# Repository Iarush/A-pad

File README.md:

# A-pad
A  custom Macropad with a special A-shaped keypad

## Specs
8 Mx Cherry Keys
EC11 Rotary Encoder
0.91" OLED Display
Seeed XIAO RP2040 Microcontroller
Custom-made PCB
Custom-made case and plates

## CAD Model

The Case is constructed using the sandwhich plating method. 3 plates were made. A bottom plate where screws are added, a middle frame amidst which the PCB rests, and finally a top switchplate for an aestheic look tht hides the screws.

### Unique Features

- Switchplate is deeply bezeled aroung the OLED to allow easier viewability
- An "island" is created at the center of the A which is compeletely seperate from other parts of the switchplate but is secured with an M3 screw.
- Rotary Encoder top is also a CAD Model
CAD was made in Onshape

## PCB Schematic

The schematic was created in KICAD with the guidance of this Joe Scotto video on matrix wiring: [Video](https://www.youtube.com/watch?v=8WXpGTIbxlQ&t=787s)

## PCB

## Firmware Overview

This hackpad uses [KMK](https://github.com/KMKfw/kmk_firmware) firmware (CircuitPython). The firmware is [Production/main.py](Production/main.py).

- The 8 keys are wired as a 3x3 diode matrix (the encoder push button is the 9th spot)
- Keys: copy / play-pause / paste on top, undo / save / redo on the crossbar, previous / next track on the legs
- The rotary encoder changes volume, press to mute
- The 8 SK6812 MINI-E LEDs run a breathing rainbow
- The OLED shows the A-Pad name and the encoder controls

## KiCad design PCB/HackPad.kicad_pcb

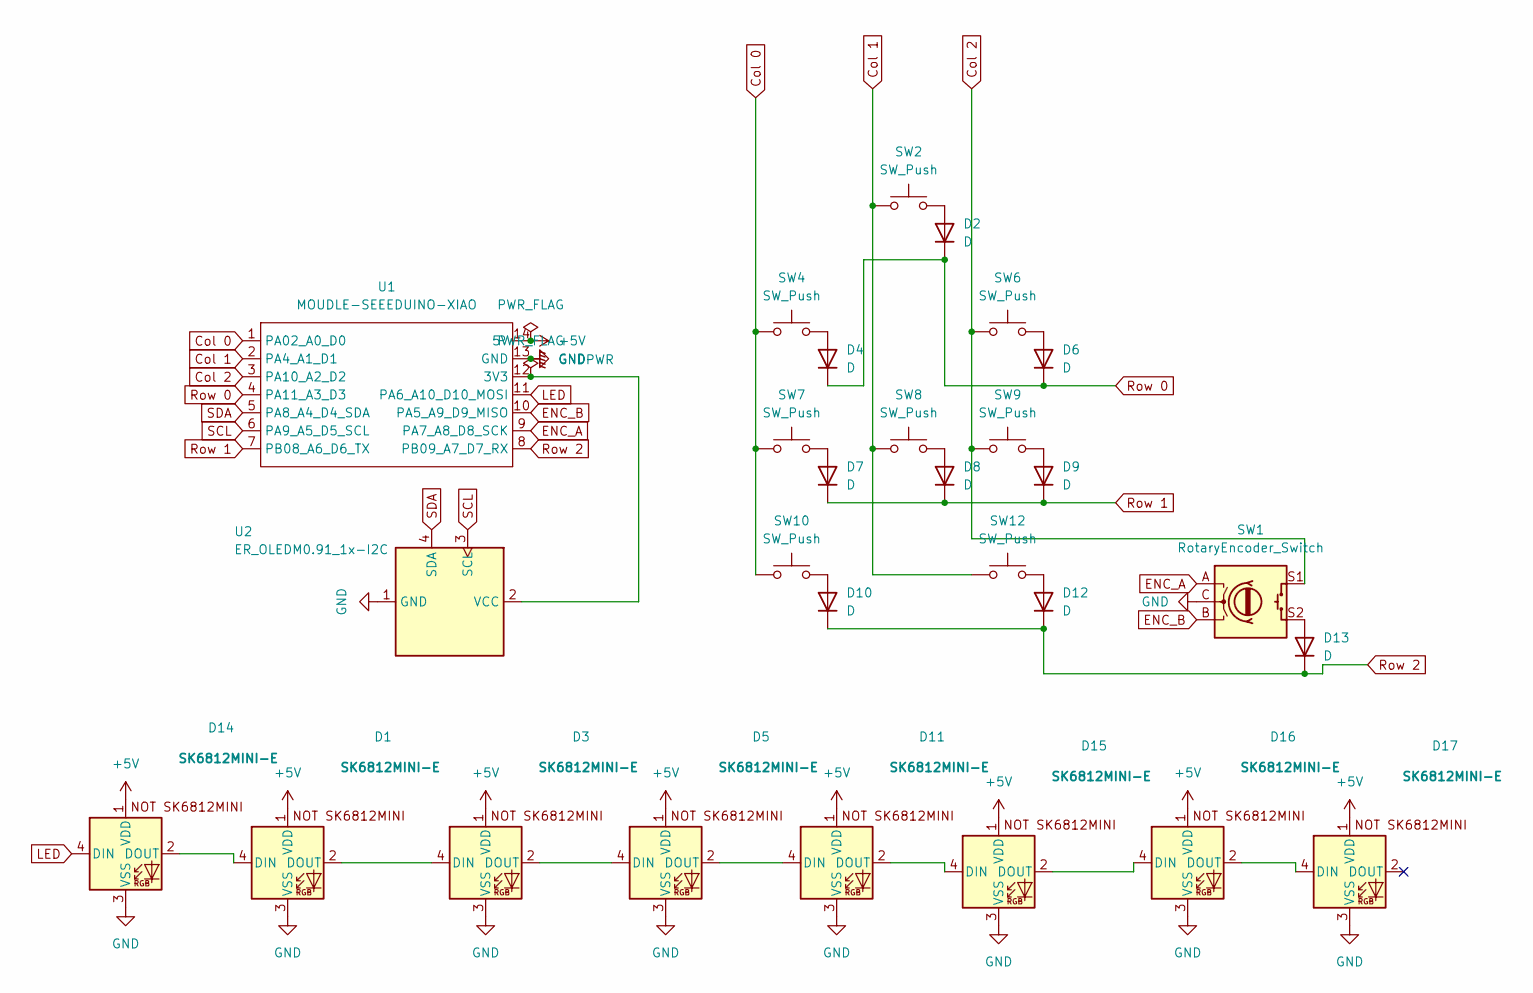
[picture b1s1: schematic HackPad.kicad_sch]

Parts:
D1, D3, D5, D11, D14, D15, D16, D17: SK6812MINI-E; SK6812MINI-E_fixed
D2, D4, D6, D7, D8, D9, D10, D12, D13: D; D_DO-35_SOD27_P7.62mm_Horizontal
SW1: RotaryEncoder_Switch; RotaryEncoder_Alps_EC11E-Switch_Vertical_H20mm
SW2, SW4, SW6, SW7, SW8, SW9, SW10, SW12: SW_Push; SW_Cherry_MX_1.00u_PCB
U1: MOUDLE-SEEEDUINO-XIAO; XIAO-Generic-Hybrid-14P-2.54-21X17.8MM
U2: ER_OLEDM0.91_1x-I2C

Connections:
+5V: D1.1 (VDD), D3.1 (VDD), D5.1 (VDD), D11.1 (VDD), D14.1 (VDD), D15.1 (VDD), D16.1 (VDD), D17.1 (VDD), U1.14 (5V)
Col 0: SW4.1, SW7.1, SW10.1, U1.1 (PA02_A0_D0)
Col 1: SW2.1, SW8.1, SW12.1, U1.2 (PA4_A1_D1)
Col 2: SW1.S1, SW6.1, SW9.1, U1.3 (PA10_A2_D2)
ENC_A: SW1.A, U1.9 (PA7_A8_D8_SCK)
ENC_B: SW1.B, U1.10 (PA5_A9_D9_MISO)
GND: D1.3 (VSS), D3.3 (VSS), D5.3 (VSS), D11.3 (VSS), D14.3 (VSS), D15.3 (VSS), D16.3 (VSS), D17.3 (VSS), SW1.C, U1.13 (GND), U2.1 (GND)
LED: D14.4 (DIN), U1.11 (PA6_A10_D10_MOSI)
unnamed: D1.4 (DIN), D14.2 (DOUT)
unnamed: D1.2 (DOUT), D3.4 (DIN)
unnamed: D2.2 (A), SW2.2
unnamed: D3.2 (DOUT), D5.4 (DIN)
unnamed: D4.2 (A), SW4.2
unnamed: D6.2 (A), SW6.2
unnamed: D7.2 (A), SW7.2
unnamed: D8.2 (A), SW8.2
unnamed: D9.2 (A), SW9.2
unnamed: D10.2 (A), SW10.2
unnamed: D5.2 (DOUT), D11.4 (DIN)
unnamed: D11.2 (DOUT), D15.4 (DIN)
unnamed: D12.2 (A), SW12.2
unnamed: D13.2 (A), SW1.S2
unnamed: D15.2 (DOUT), D16.4 (DIN)
unnamed: D16.2 (DOUT), D17.4 (DIN)
unnamed: U1.12 (3V3), U2.2 (VCC)
Row 0: D2.1 (K), D4.1 (K), D6.1 (K), U1.4 (PA11_A3_D3)
Row 1: D7.1 (K), D8.1 (K), D9.1 (K), U1.7 (PB08_A6_D6_TX)
Row 2: D10.1 (K), D12.1 (K), D13.1 (K), U1.8 (PB09_A7_D7_RX)
SCL: U1.6 (PA9_A5_D5_SCL), U2.3 (SCL)
SDA: U1.5 (PA8_A4_D4_SDA), U2.4 (SDA)

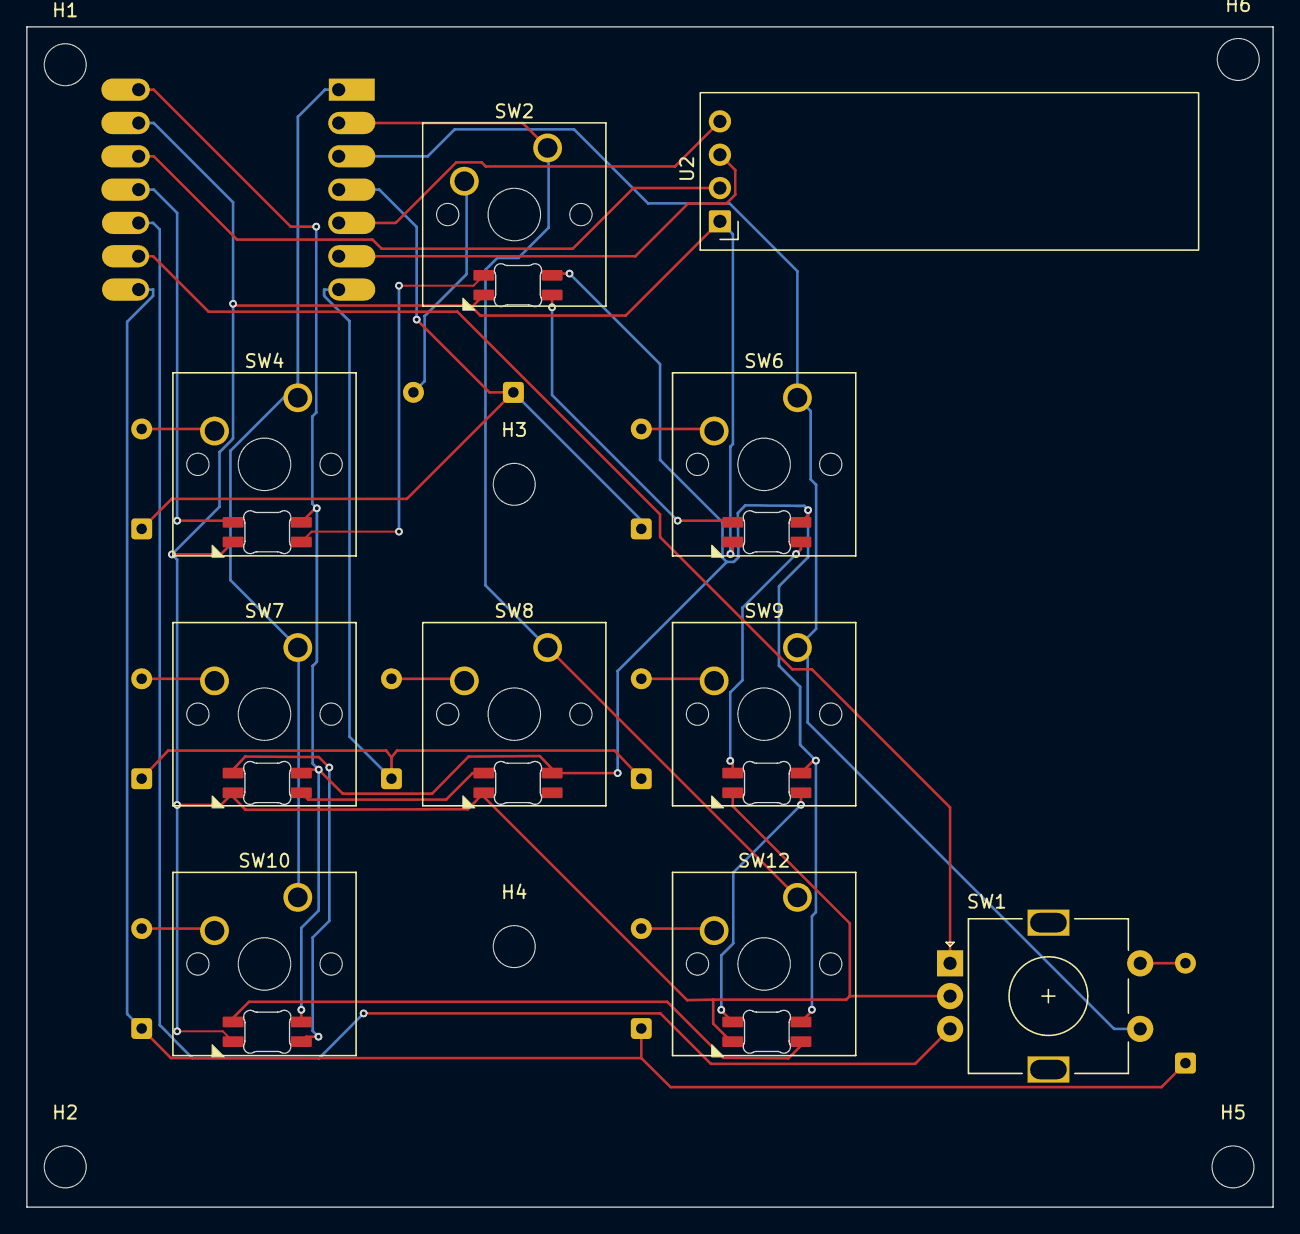
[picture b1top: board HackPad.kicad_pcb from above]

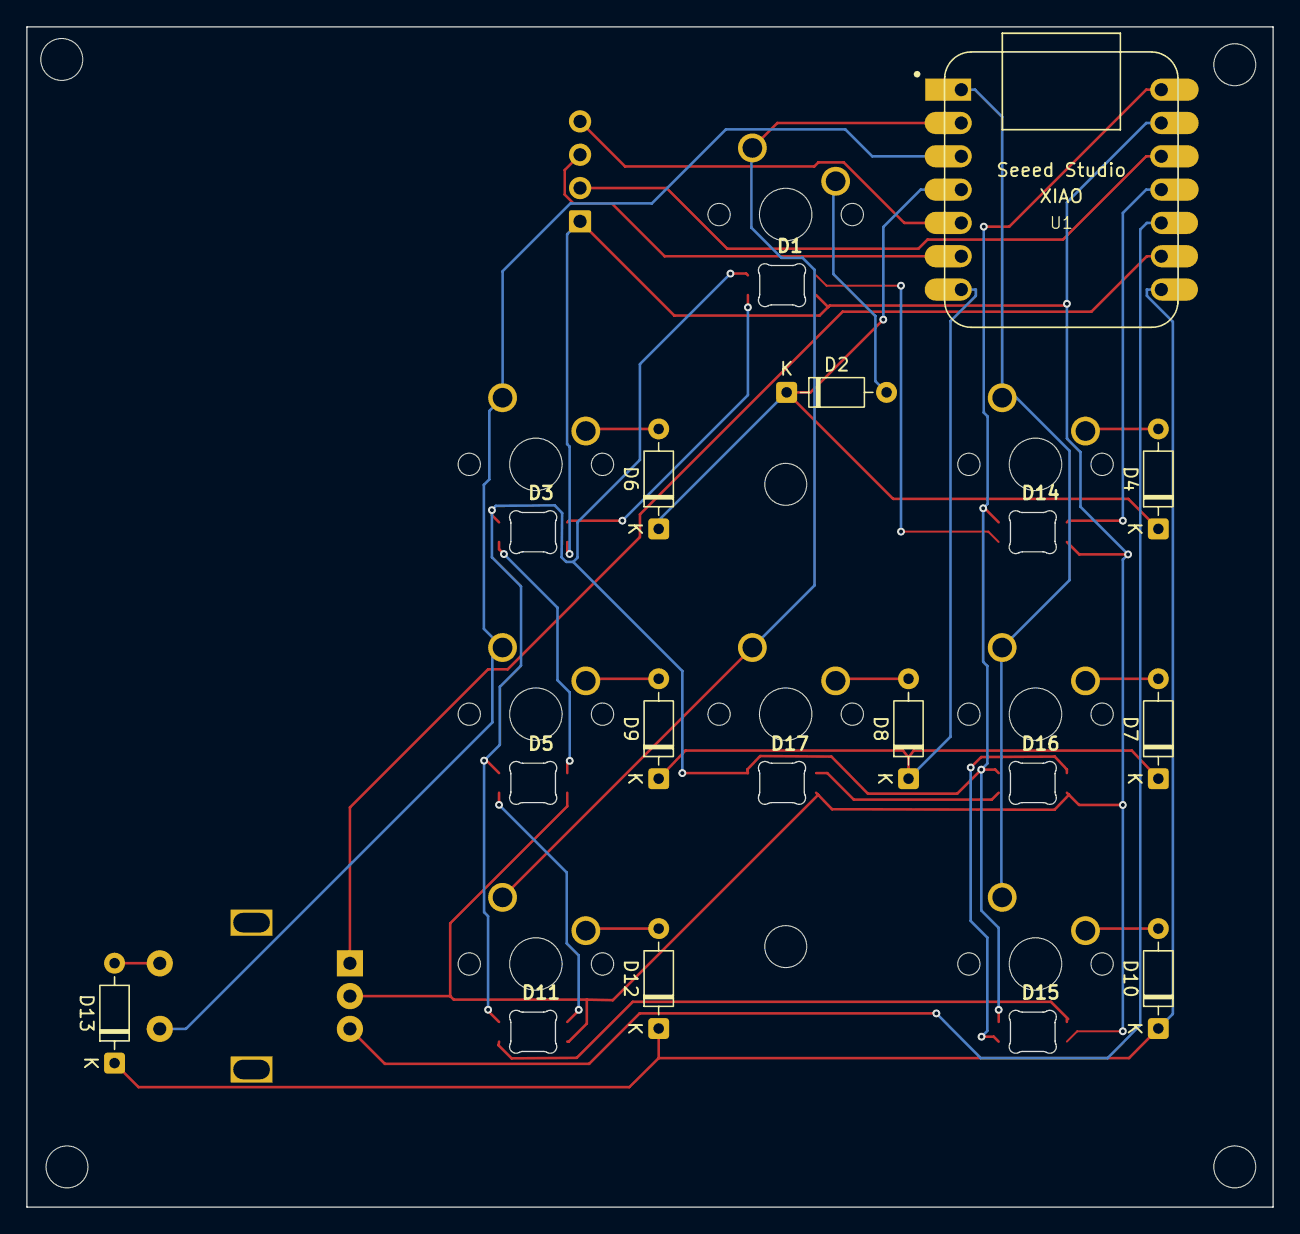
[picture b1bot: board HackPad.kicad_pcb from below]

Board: 2 copper layers, 95.0 x 90.0 mm, 34 parts (18 on the bottom side), 30 nets.

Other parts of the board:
H1, H2, H3, H4, H5, H6: MountingHole; MountingHole_3.2mm_M3
